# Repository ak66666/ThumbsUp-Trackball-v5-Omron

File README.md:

# ThumbsUp! Trackball v5 Omron
A version of v3 with Omron D2FC-7 switches used instead of Kailh Chocs.
PCB is used as button caps.

Finger-controlled configuration.

For the thumb-operated mode a back(top) palm support is included.
For the right-hand operation mirror the model in slicer.

A PCB-based thumb-operated trackball, inspired by Elecom EX-G left hand trackball, Ploopy Nano trackball, and my own ThumbsUp! keyboards.

To be suitable for both left- and right-hand usage (in "portrairt" orientation), and also be finger-operated (in "landscape").
A three-position switch/soldering pad tells the device which mode to use - that will define the rotating direction.

It is a continuation of Trackball v3 - with the Kailh Choc switches replaced with Omron mouse buttons.
 
For MCU nice!nano v2 (and clones) with ZMK-based firmware is used (wired or wireless through Bluetooth or a dongle.)

34 mm ball, same as in Elecom EX-G.
For bearings - uxcell 2.5mm Ceramic Bearing Balls, ZrO2 Zirconium Oxide Ball, again, the same as used to improve my Elecom trackballs.
Bearings to be implanted into PCBs, no 3D-printed ball shroud/holder.

Other pictures in Photos folder.

# Firmware - same as v3

Original version with BT and wired connection:
https://github.com/ak66666/zmk-config-trackball.v3        

Dongle version:
https://github.com/ak66666/zmk-config-trackball.v3.dongle

Dongle version for a combo with ThumbsUp! v9 keyboard:
https://github.com/ak66666/zmk-config-trackball-v3-and-keyboard-v9.dongle

# For sale on Etsy
 
https://www.etsy.com/ca/listing/4390955764

# Assembly Instructions

Similar to v3:
https://thumbsupkeyboards.blogspot.com/2025/09/thumbsup-trackball-v3-assembly-steps.html

The difference is in the switches only.
3D printed switch bases are needed.
Below the switches there are three-point soldering connectors - you need to close two of them on the side where the switch button is.

# Gerber Generation

There is a little trick that needs to be applied to produce silkscreens with overlapping labels.
Normally all the elements on the silkscreen are added up, so the text would be interrupted/covered by the drawing elements.

To work around that limitation - use the generation option "Subtract Soldermask from Silkscreen".
IMPORTANT: Save and preserve the project files, you will be temporarily removing parts of the board design.

Labels which are covered by the silkscreen pattern, they should be moved to the front/back soldering mask layer.
Text needs to be inverted - check "Knockout" box in the label properties.
On the matching front/back silkscreen layer add a rectangle around the label. 
For the design time leave it unfilled - will fill it during Gerber file generation as described below.

To generate fabrication files:
- In PCB Editor, for each of the PCB do the following (_do not_ save the file while doing that):
	- Select and delete all other PCBs, leave only one to be generated.
	- For each label on the solder mask layer - locate silkscreen rectangles around that label, modify its property - check "Filled Shape" box.
	  (Those boxes are not filled while designing the board, otherwise they cover all other elements.)
	- Generate the Gerbers (plotting, drilling files) with this:
		- Uncheck  "Subtract Soldermask from Silkscreen" option.
		- Exlude the silkscreens at this point.
	- Generate silkscreen layers with  "Subtract Soldermask from Silkscreen" option checked.
	- Close PCB Editor without saving the file.
	- Re-open PCB Editor and repeat these steps for other boards.
- Verify the genearted files.

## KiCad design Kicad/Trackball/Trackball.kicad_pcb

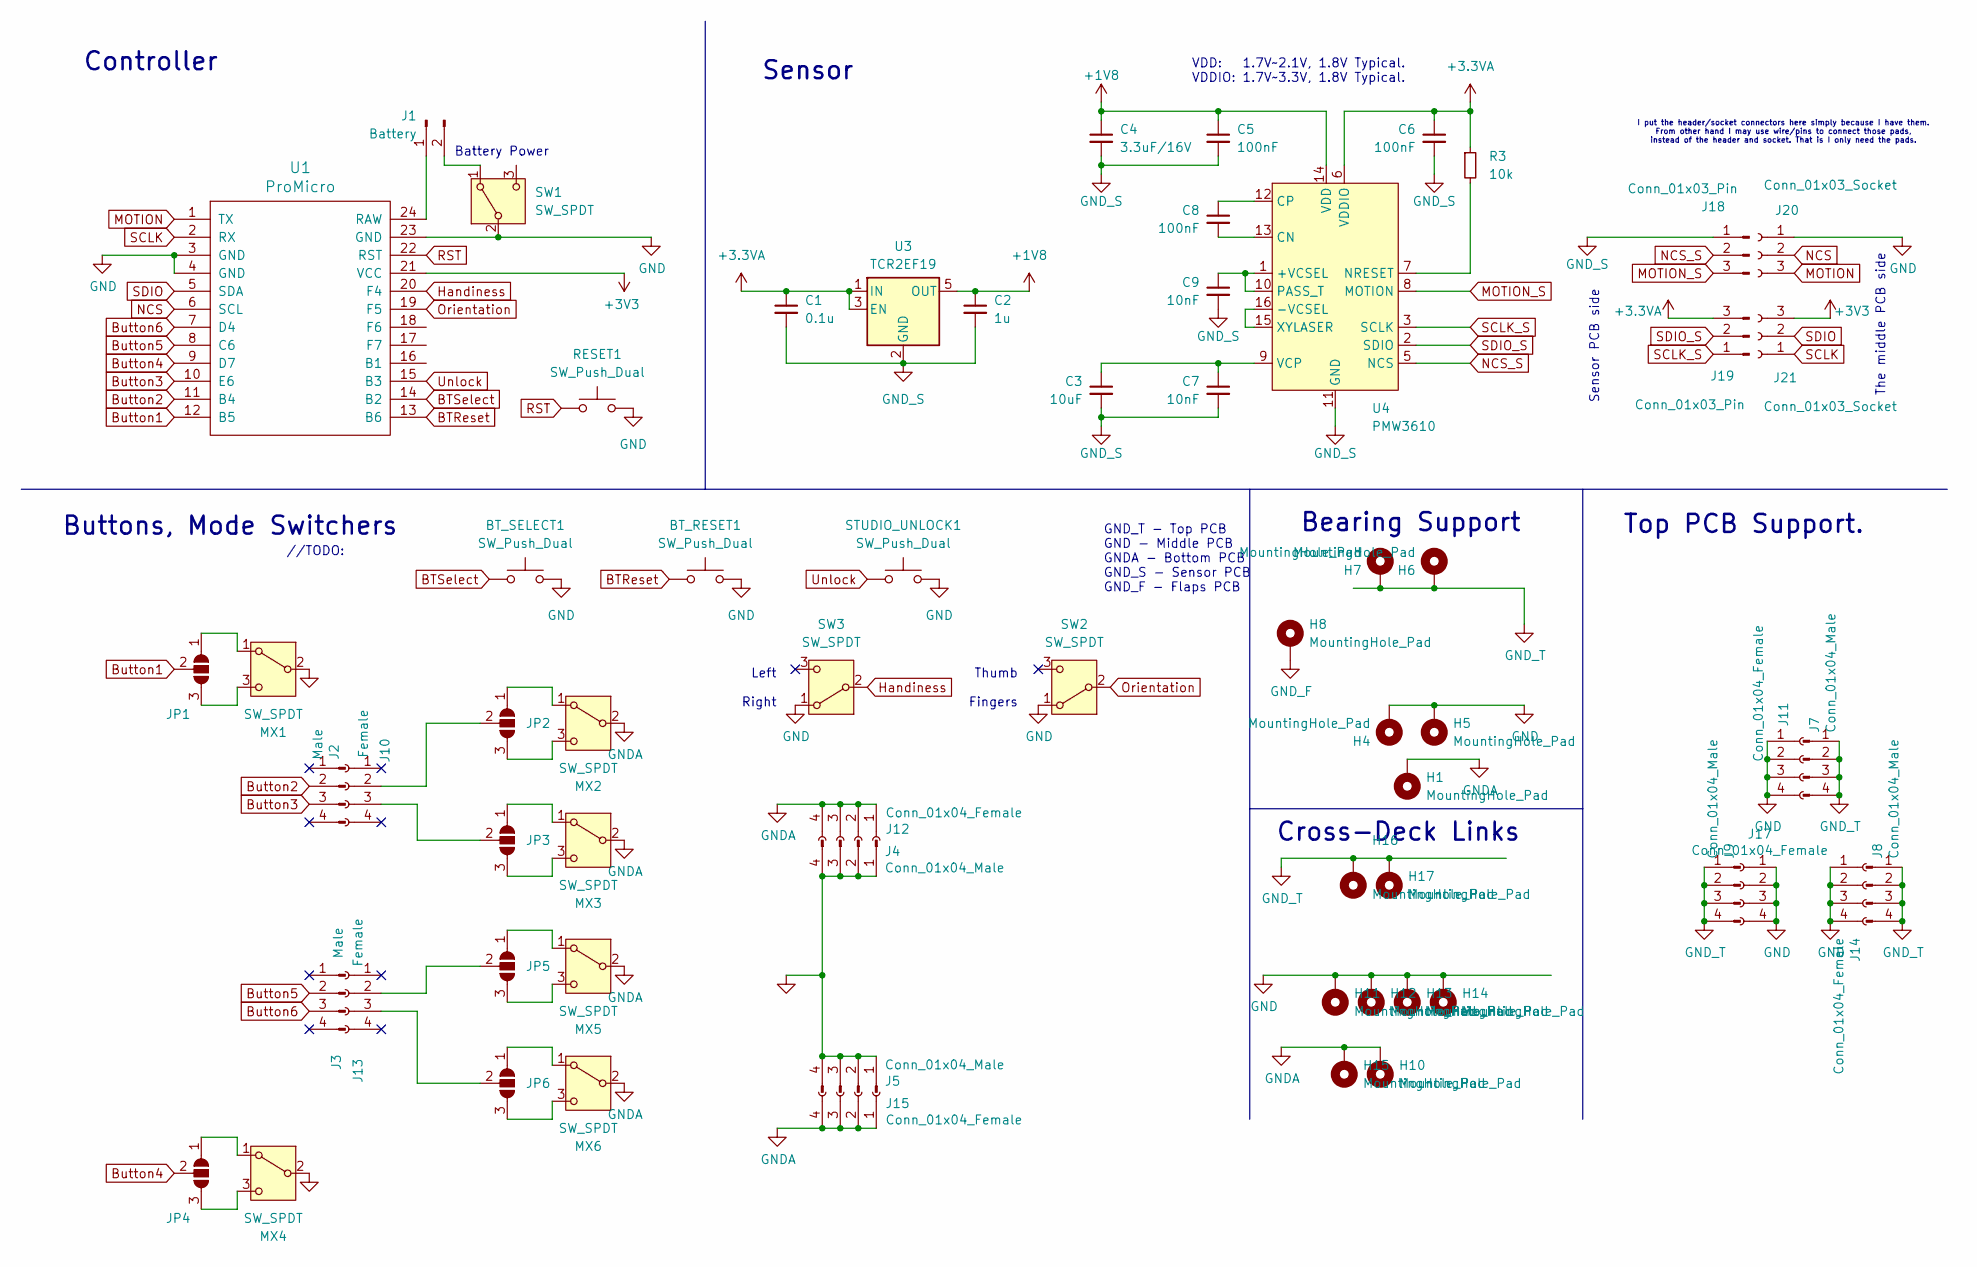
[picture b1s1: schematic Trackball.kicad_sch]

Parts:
BT_RESET1: SW_Push_Dual; SW_Push_1P1T_NO_CK_KSC6xxJ
BT_SELECT1: SW_Push_Dual; SW_Push_1P1T_NO_CK_KSC6xxJ
C1: 0.1u; C_0402_1005Metric
C2: 1u; C_0402_1005Metric
C3: 10uF; C_0402_1005Metric; MFR. Part # CL21A106KAYNNNE; JLCPCB Part # C15850
C4: 3.3uF/16V; C_0805_2012Metric; MFR. Part # TCC0805X7R335K250FT; JLCPCB Part # C7393948
C5, C6, C8: 100nF; C_0402_1005Metric; MFR. Part # CC0603KRX7R9BB104; JLCPCB Part # C14663
C7, C9: 10nF; C_0402_1005Metric; MFR. Part # 0603B103K500NT; JLCPCB Part # C57112
H1, H4, H5, H6, H7, H8: MountingHole_Pad; MountingHole_2.5mm_Pad
H10, H11, H12, H13, H14, H15, H16, H17: MountingHole_Pad; MountingHole_3.5mm_Pad
J1: Battery; PinHeader_1x02_P2.54mm_Vertical
J2, J3: Male; PinHeader_1x04_P2.54mm_Vertical
J4, J5, J7, J8, J9: Conn_01x04_Male; PinHeader_1x04_P2.54mm_Vertical
J10, J13: Female; PinSocket_1x04_P2.54mm_Vertical
J11, J12, J14, J15, J17: Conn_01x04_Female; PinSocket_1x04_P2.54mm_Vertical
J18, J19: Conn_01x03_Pin; PinHeader_1x03_P2.54mm_Vertical
J20, J21: Conn_01x03_Socket; PinSocket_1x03_P2.54mm_Vertical
JP1, JP2, JP3, JP4, JP5, JP6: SolderJumper_3_Open; SolderJumper-3_P1.3mm_Open_RoundedPad1.0x1.5mm
MX1, MX2, MX3, MX4, MX5, MX6: SW_SPDT; SW_D2FC_OMR
R3: 10k; R_0603_1608Metric; MFR. Part # 0603WAF1002T5E; JLCPCB Part # C25804
RESET1: SW_Push_Dual; SW_Push_1P1T_NO_CK_KSC6xxJ
STUDIO_UNLOCK1: SW_Push_Dual; SW_Push_1P1T_NO_CK_KSC6xxJ
SW1, SW2, SW3: SW_SPDT; 18252321
U1: ProMicro
U3: TCR2EF19; SOT-23-5
U4: PMW3610; PMW3610DM-SUDU 16Pin; MFR. Part # PMW3610DM-SUDU; JLCPCB Part # C42442560

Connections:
+1V8: C2.1, C4.1, C5.1, U3.5 (OUT), U4.14 (VDD)
+3.3VA: C1.1, C6.1, J19.3, R3.1, U3.1 (IN), U3.3 (EN), U4.6 (VDDIO)
+3V3: J21.3, U1.21 (VCC)
BTReset: BT_RESET1.1, U1.13 (B6)
BTSelect: BT_SELECT1.1, U1.14 (B2)
Button1: JP1.2 (C), U1.12 (B5)
Button2: J2.2, U1.11 (B4)
Button3: J2.3, U1.10 (E6)
Button4: JP4.2 (C), U1.9 (D7)
Button5: J3.2, U1.8 (C6)
Button6: J3.3, U1.7 (D4)
GND: BT_RESET1.2, BT_SELECT1.2, H4.1, H5.1, H11.1, H12.1, H13.1, H14.1, J4.1, J4.2, J4.3, J4.4, J5.1, J5.2, J5.3, J5.4, J11.1, J11.2, J11.3, J11.4, J14.1, J14.2, J14.3, J14.4, J17.1, J17.2, J17.3, J17.4, J20.1, MX1.2 (B), MX4.2 (B), RESET1.2, STUDIO_UNLOCK1.2, SW1.2 (B), SW2.1 (A), SW3.1 (A), U1.3 (GND), U1.4 (GND), U1.23 (GND)
GNDA: H1.1, H10.1, H15.1, J12.1, J12.2, J12.3, J12.4, J15.1, J15.2, J15.3, J15.4, MX2.2 (B), MX3.2 (B), MX5.2 (B), MX6.2 (B)
GND_F: H8.1
GND_S: C1.2, C2.2, C3.2, C4.2, C5.2, C6.2, C7.2, C9.2, J18.1, U3.2 (GND), U4.11 (GND)
GND_T: H6.1, H7.1, H16.1, H17.1, J7.1, J7.2, J7.3, J7.4, J8.1, J8.2, J8.3, J8.4, J9.1, J9.2, J9.3, J9.4
Handiness: SW3.2 (B), U1.20 (F4)
MOTION: J20.3, U1.1 (TX)
MOTION_S: J18.3, U4.8 (MOTION)
NCS: J20.2, U1.6 (SCL)
NCS_S: J18.2, U4.5 (NCS)
unnamed: J1.1, U1.24 (RAW)
unnamed: J1.2, SW1.1 (A)
unnamed: J10.2, JP2.2 (C)
unnamed: J10.3, JP3.2 (C)
unnamed: J13.2, JP5.2 (C)
unnamed: J13.3, JP6.2 (C)
unnamed: JP1.1 (A), MX1.1 (A)
unnamed: JP1.3 (B), MX1.3 (C)
unnamed: JP2.1 (A), MX2.1 (A)
unnamed: JP2.3 (B), MX2.3 (C)
unnamed: JP3.1 (A), MX3.1 (A)
unnamed: JP3.3 (B), MX3.3 (C)
unnamed: JP4.1 (A), MX4.1 (A)
unnamed: JP4.3 (B), MX4.3 (C)
unnamed: JP5.1 (A), MX5.1 (A)
unnamed: JP5.3 (B), MX5.3 (C)
unnamed: JP6.1 (A), MX6.1 (A)
unnamed: JP6.3 (B), MX6.3 (C)
unnamed: C9.1, U4.1 (+VCSEL), U4.10 (PASS_T)
unnamed: U4.15 (XYLASER), U4.16 (-VCSEL)
unnamed: C8.2, U4.13 (CN)
unnamed: C8.1, U4.12 (CP)
unnamed: R3.2, U4.7 (NRESET)
unnamed: C3.1, C7.1, U4.9 (VCP)
Orientation: SW2.2 (B), U1.19 (F5)
RST: RESET1.1, U1.22 (RST)
SCLK: J21.1, U1.2 (RX)
SCLK_S: J19.1, U4.3 (SCLK)
SDIO: J21.2, U1.5 (SDA)
SDIO_S: J19.2, U4.2 (SDIO)
Unlock: STUDIO_UNLOCK1.1, U1.15 (B3)

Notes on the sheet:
//TODO:
VDD: 1.7V~2.1V, 1.8V Typical. VDDIO: 1.7V~3.3V, 1.8V Typical.
Battery Power
I put the header/socket connectors here simply because I have them. From other hand I may use wire/pins to connect those pads, instead of the header and socket. That is I only need the pads.
GND_T - Top PCB GND - Middle PCB GNDA - Bottom PCB GND_S - Sensor PCB GND_F - Flaps PCB
Top PCB Support.
The middle PCB side
Sensor PCB side
Thumb Fingers
Buttons, Mode Switchers
Controller
Bearing Support
Cross-Deck Links
Sensor
Left Right

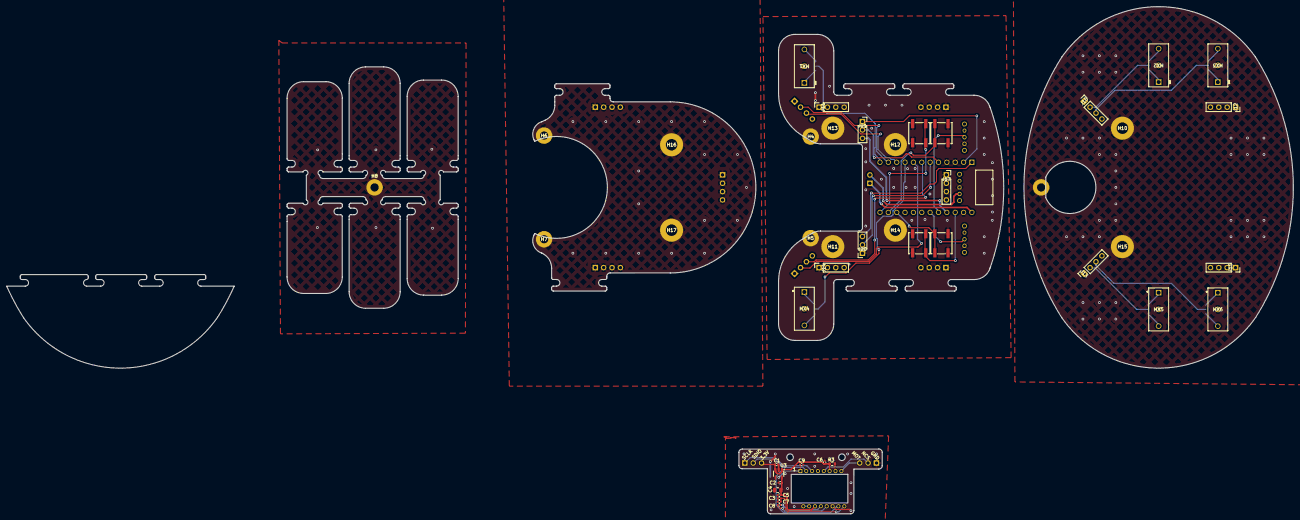
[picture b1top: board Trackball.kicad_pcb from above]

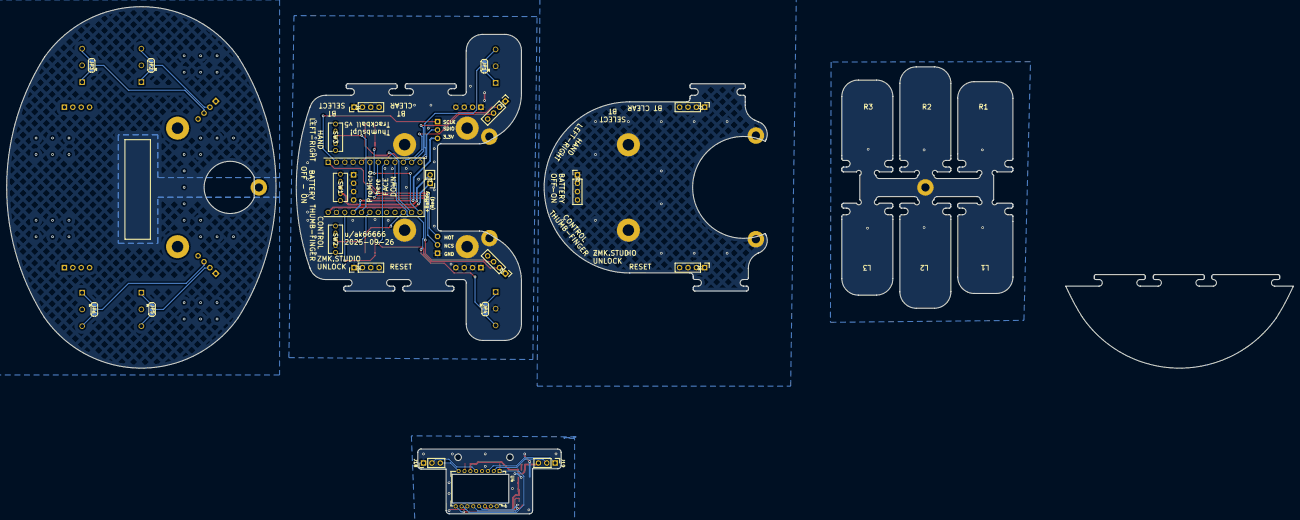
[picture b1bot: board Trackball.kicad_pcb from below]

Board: 2 copper layers, 391.0 x 154.1 mm, 65 parts (20 on the bottom side), 51 nets.

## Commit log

2025-09-26 B5: First draft version.
2025-09-26 B5: Replaced switches, added soldering pad switches to configure the button switch orientation, added break-outs to detach the flaps over the switches.
2025-09-26 B5: Tried to upload to JLC, corrected the labels, error-checked.
2025-09-26 B5: As ordered 20250926.
2025-10-11 B5: Separated key flaps into a separate panel. Added photos of rev.1 device.
2025-10-11 B5: Fixed the validation errors, ready to regenerate Gerbers
2025-10-11 B5: Created Gerbers, loaded them to JLCPCB, not ordered yet.
2025-10-21 B5: Added photos, updated readme.
2025-10-24 B5: Modified the flaps plate - changed their length as per user feedback. Updated Gerbers for that plate, ordered that plate 20251024.
2025-10-26 B5: Added a 3D-printed palm support piece.
2025-10-31 B5: Corrected the 3D-printed palm support piece, now it properly fits in its place.
2025-12-05 B3: Replaced the dongle files.
2026-02-05 B5: Uploaded STEP files for the plates
2026-05-03 B5: Rev.1 changes.
2026-05-03 B5: Refreshed Gerbers, as ordered 2026-05-03.
2026-05-23 B5: Photos added.
